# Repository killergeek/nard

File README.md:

# NARD
NARD: a dual sim/sam card interface for the flipper zero

# INFO
Its made to make working with smart card interface type ISO7816 easier on the flipper.\
It fits on top of the flipper with a easy breakout on the back so the IO is still available and you can plug in other modules.\
Just make sure those are not using PC0 and PC1. because those are used on the NARD.\
PC0 and PC1 are used as a serial port to communicate with the SEC1210.

When you buy the SEC1210 make sure its the UART version **not the USB!**\
And they come pre programmed with firmware from Microchip.\
And use the CCID commands to interface: https://www.usb.org/sites/default/files/DWG_Smart-Card_CCID_Rev110.pdf

For information about how to communicate with the SEC1210: https://microchip.my.site.com/s/article/SEC1210-URT--Minimal-UART-Testing-on-Windows

Example of a serial command send to the SEC1210:

See below details for this CCID command (hex):\
Hex Bytes: `03 06 62 00 00 00 00 01 01 00 00 00 67`\
*Byte 0 : SYNC (`0x03`)\
 *Byte 1 : CTRL (`0x06`)\
 *Byte 2 onwards:10 bytes of CCID header + data length: CCID command\
 *Last Byte: LRC (XOR of all the previous bytes)

so: SYNC, CTRL, <CCID commmand>, LRC

The SEC1210 information: https://www.microchip.com/en-us/product/SEC1210

sim card slot used. \
slot1: 115J-BCO0 \
slot2: 115J-ACO0 \
you can find the sim sockets by https://www.tme.eu/

slot1 has the 2 extra pads C4 and C8.

***
simple list of items used:\
\
TME.EU\
115J-ACO0 ATTEND\
115J-BCO0 ATTEND\
\
MOUSER.com\
\
855-M20-7910842R\
200-SMH11002TSTR\
81-BLM18EG221SN1D\
71-CRCW0402J-43-E3\
187-CL05A105KO5NNNC\
81-GRM155R61A104KA01\
187-CL05A106MP6NUN8\
187-CL05A106MP6NUN8\
279-CRG0402J100K/10\
71-CRCW04021M00JNEDC\
652-CR0402JW-331GLF\
579-SEC1210IPVUR2\
743-IN-S21AT5R
***

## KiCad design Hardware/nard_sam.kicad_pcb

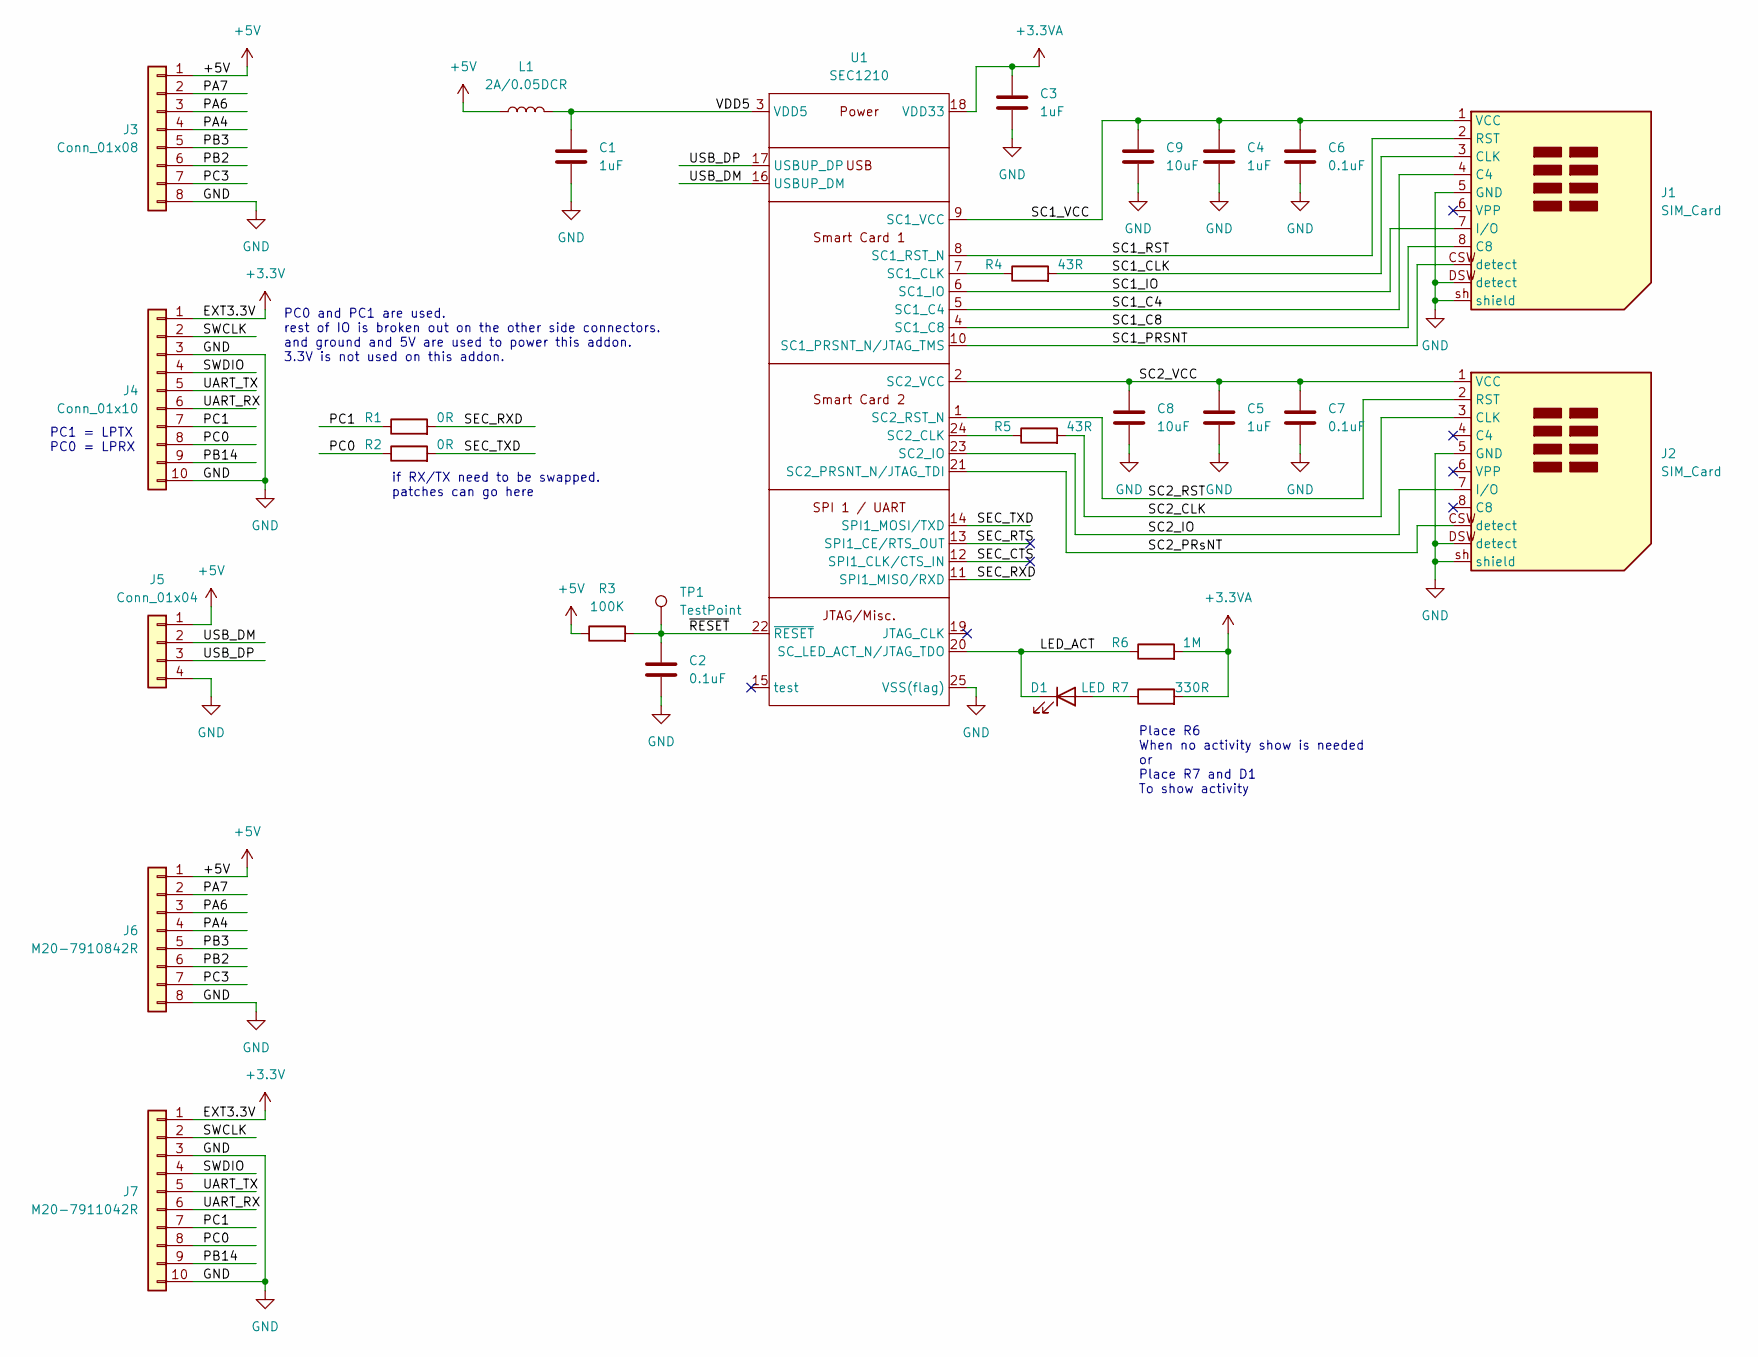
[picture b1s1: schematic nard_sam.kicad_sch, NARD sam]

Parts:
C1, C3, C4, C5: 1uF; C_0402_1005Metric; JLCPCB Part # C29266
C2, C6, C7: 0.1uF; C_0402_1005Metric; JLCPCB Part # C169292
C8, C9: 10uF; C_0402_1005Metric; JLCPCB Part # C3902158
D1: LED; LED_0201_0603Metric; JLCPCB Part # C3646923
J1, J2: SIM_Card; mixed_sim_sam_card_holder; JLCPCB Part # C5174695
J3: Conn_01x08; PinHeader_1x08_P2.54mm_Vertical_SMD_Pin1Left; JLCPCB Part # C2883765
J4: Conn_01x10; PinHeader_1x10_P2.54mm_Vertical_SMD_Pin1Left; JLCPCB Part # C2883767
J5: Conn_01x04; usb pads breakout
J6: M20-7910842R; m20-7910842
J7: M20-7911042R; m20-7911042
L1: 2A/0.05DCR; L_0603_1608Metric; JLCPCB Part # C85827
R1, R2: 0R; R_0402_1005Metric; JLCPCB Part # C21376
R3: 100K; R_0402_1005Metric; JLCPCB Part # C427222
R4, R5: 43R; R_0402_1005Metric; JLCPCB Part # C412915
R6: 1M; R_0402_1005Metric; JLCPCB Part # C427228
R7: 330R; R_0402_1005Metric; JLCPCB Part # C427206
TP1: TestPoint; TestPoint_Pad_D1.0mm
U1: SEC1210; QFN-24-1EP_5x5mm_P0.65mm_EP3.2x3.2mm; JLCPCB Part # C633309

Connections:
+3.3V: J4.1, J7.1
+3.3VA: C3.1, R6.2, R7.2, U1.18 (VDD33)
+5V: J3.1, J5.1, J6.1, L1.1, R3.1
/LED_ACT: D1.1 (K), R6.1, U1.20 (SC_LED_ACT_N/JTAG_TDO)
/PA4: J3.4, J6.4
/PA6: J3.3, J6.3
/PA7: J3.2, J6.2
/PB2: J3.6, J6.6
/PB3: J3.5, J6.5
/PB14: J4.9, J7.9
/PC0: J4.8, J7.8, R2.1
/PC1: J4.7, J7.7, R1.1
/PC3: J3.7, J6.7
/SC1_C4: J1.4 (C4), U1.5 (SC1_C4)
/SC1_C8: J1.8 (C8), U1.4 (SC1_C8)
/SC1_CLK: J1.3 (CLK), R4.2; also elsewhere on the board
/SC1_IO: J1.7 (I/O), U1.6 (SC1_IO); also elsewhere on the board
/SC1_PRSNT: J1.CSW (detect), U1.10 (SC1_PRSNT_N/JTAG_TMS); also elsewhere on the board
/SC1_RST: J1.2 (RST), U1.8 (SC1_RST_N); also elsewhere on the board
/SC1_VCC: C4.1, C6.1, C9.1, J1.1 (VCC), U1.9 (SC1_VCC); also elsewhere on the board
/SC2_CLK: J2.3 (CLK), R5.2
/SC2_IO: J2.7 (I/O), U1.23 (SC2_IO)
/SC2_PRsNT: J2.CSW (detect), U1.21 (SC2_PRSNT_N/JTAG_TDI)
/SC2_RST: J2.2 (RST), U1.1 (SC2_RST_N)
/SC2_VCC: C5.1, C7.1, C8.1, J2.1 (VCC), U1.2 (SC2_VCC)
/SEC_CTS: U1.12 (SPI1_CLK/CTS_IN)
/SEC_RTS: U1.13 (SPI1_CE/RTS_OUT)
/SEC_RXD: R1.2, U1.11 (SPI1_MISO/RXD)
/SEC_TXD: R2.2, U1.14 (SPI1_MOSI/TXD)
/SWCLK: J4.2, J7.2
/SWDIO: J4.4, J7.4
/UART_RX: J4.6, J7.6
/UART_TX: J4.5, J7.5
/USB_DM: J5.2, U1.16 (USBUP_DM)
/USB_DP: J5.3, U1.17 (USBUP_DP)
/VDD5: C1.1, L1.2, U1.3 (VDD5)
/~RESET: C2.1, R3.2, TP1.1, U1.22 (~RESET)
GND: C1.2, C2.2, C3.2, C4.2, C5.2, C6.2, C7.2, C8.2, C9.2, J1.5 (GND), J1.DSW (detect), J1.sh (shield), J2.5 (GND), J2.DSW (detect), J2.sh (shield), J3.8, J4.3, J4.10, J5.4, J6.8, J7.3, J7.10, U1.25 (VSS(flag)); also elsewhere on the board
unnamed: D1.2 (A), R7.1
unnamed: R4.1, U1.7 (SC1_CLK)
unnamed: R5.1, U1.24 (SC2_CLK)

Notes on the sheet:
Place R6 When no activity show is needed or Place R7 and D1 To show activity
PC1 = LPTX PC0 = LPRX
if RX/TX need to be swapped. patches can go here
PC0 and PC1 are used. rest of IO is broken out on the other side connectors. and ground and 5V are used to power this addon. 3.3V is not used on this addon.

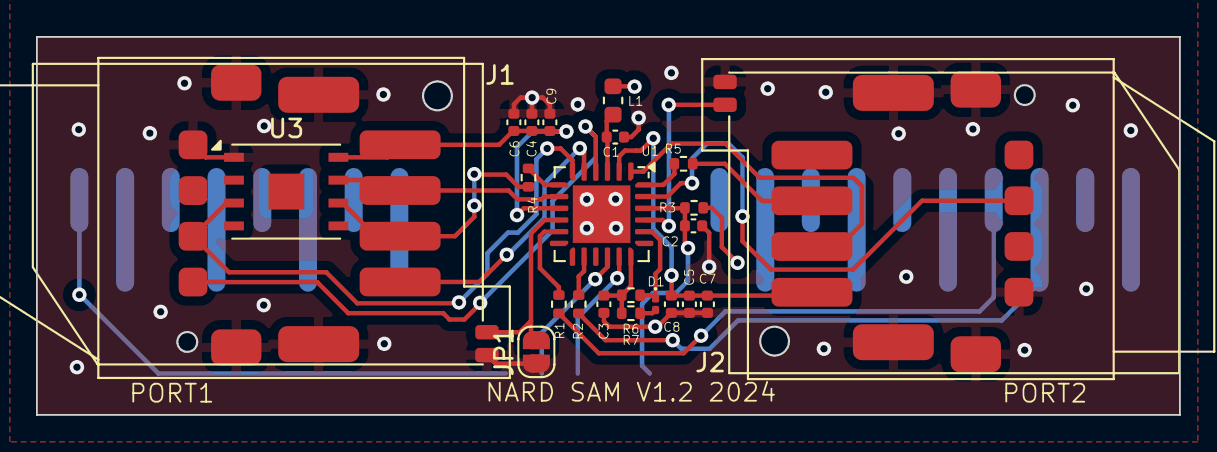
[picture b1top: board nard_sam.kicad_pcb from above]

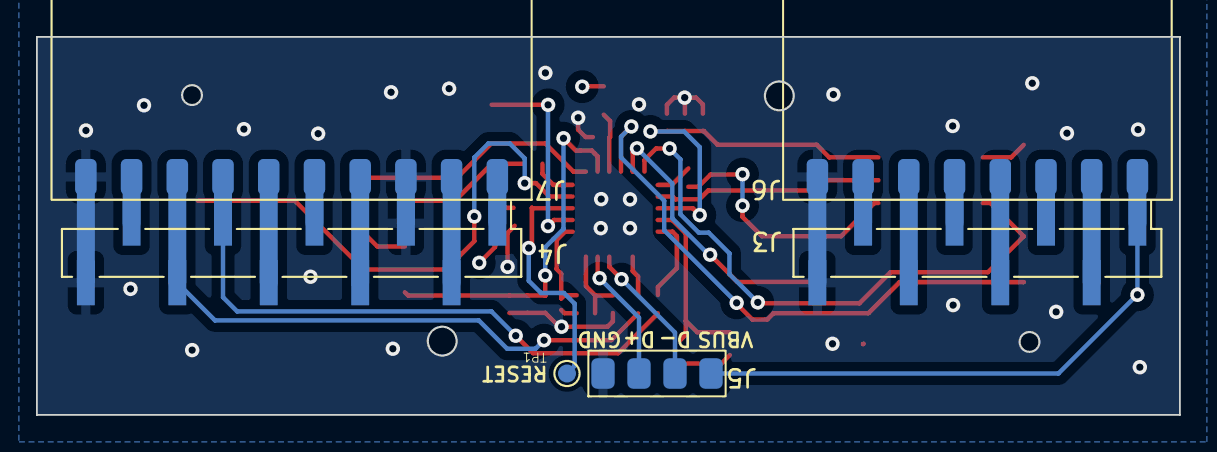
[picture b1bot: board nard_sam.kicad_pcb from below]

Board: 4 copper layers, 63.5 x 21.0 mm, 29 parts (6 on the bottom side), 39 nets.

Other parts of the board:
JP1: hardwire detect; SolderJumper-2_P1.3mm_Open_RoundedPad1.0x1.5mm
U3: ST4SIM-200M

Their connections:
/SC1_CLK: U3.6 (CLK); also elsewhere on the board
/SC1_IO: U3.3 (I/O); also elsewhere on the board
/SC1_PRSNT: JP1.2 (B); also elsewhere on the board
/SC1_RST: U3.7 (RST); also elsewhere on the board
/SC1_VCC: U3.8 (VCC); also elsewhere on the board
GND: JP1.1 (A), U3.1 (GND); also elsewhere on the board

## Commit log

2023-03-04 Update README.md
    added more info about the project and how to communicate
2023-03-04 Added hardware design. V1.1
2023-03-04 removed backup
2023-03-05 Update README.md
    added info of the sim sockets
2023-03-05 Update README.md
    typo
2023-03-11 Create pictures
    added folder for pictures
2023-03-11 Add files via upload
    added pictures of the board
2023-04-07 Update README.md
    added quick and dirty parts list of items used.
2024-11-25 added kicad backups to gitignore
2024-11-25 added footprint for placing a eSIM chip directly on the PCB
